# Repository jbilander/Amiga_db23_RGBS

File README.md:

# Amiga_DB23_RGBS
A small PCB with RGBS out from the Amiga d-sub db23 connector. Made with KiCad 5.1.2-1

### Updated v2 PCB

On request I made an updated PCB with the capacitor pads removed, 2 mm hole pitch giving two more GND holes. A little rerouting as well to provide for easier soldering when using cables with shielded wire pairs (signal + ground return). This PCB is not tested yet!

***

Update: On some cables I got a lot of noise/interference in the signal and needed to connect the shielding on the plugs on each end `d-sub metal shield <-> SCART metal shield` to get rid of it.

***

***

***

Let's solder this one. I used `220uF 16V size 1210` as coupling capacitors for the RGB pads. All resistors `size 1206`, I used the following values `R1: 330 Ohm, R2: 1K Ohm, R3: 75 Ohm`, following Stedy's guide here: The Ultimate SCART cable v1.1 http://www.ianstedman.co.uk/Amiga/amiga_hacks/Amiga_SCART/amiga_scart.html Not using pin 13 though as ground return but rather following this picture: https://ilesj.files.wordpress.com/2012/01/amiga_rgb-scart-diagram.png

***
I used an old DVI<->Vga cable that I butchered cutting off the plugs on both ends. I also found an old composite rca cable yellow-red-white laying around. I used the red-white part for the Audio. When making a cable with a SCART plug it makes sense to run the Left/Right audio wires inside the cable since the connector has both RGB video and stereo audio pins as standard. You can run the audio wires separately should you want to.

<br /><br />
I started with soldering the audio wires to the extension sides, holes with the "interconnected" symbol.
<br />

***

And then the rest, I used the three shielded wires for the RGB lines.

***

Moment of truth, hooking it up to the Amiga and yes it does work...I noticed I get more subtle vertical stripes with this cable then other Scart's I have tried, However I can still notice some "jailbars", check the last picture here from the game Another World. This is on my old Samsung LCD from 2005 that has seen better days. It is better on my plasma.

***

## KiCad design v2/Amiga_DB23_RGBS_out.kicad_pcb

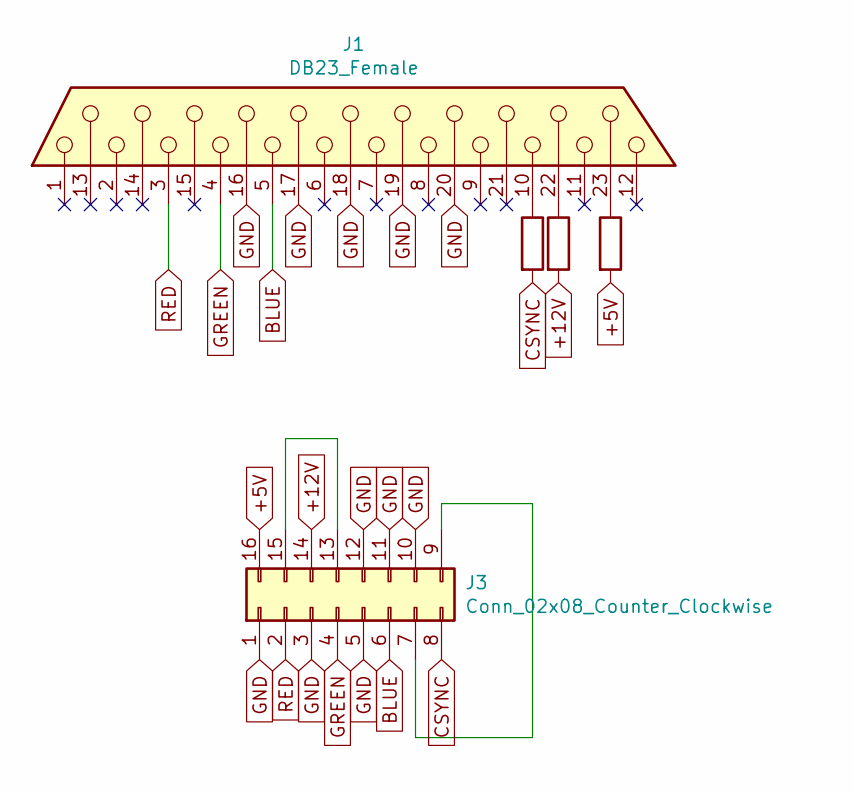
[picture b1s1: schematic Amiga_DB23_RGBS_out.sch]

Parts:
J1: DB23_Female; DSUB-23_Female_EdgeMount_P2.77mm
J3: Conn_02x08_Counter_Clockwise; PinHeader_2x08_P2.00mm_Vertical
R1: R330; R_1206_3216Metric_Pad1.42x1.75mm_HandSolder
R2: R; C_1206_3216Metric_Pad1.42x1.75mm_HandSolder
R3: R110; C_1206_3216Metric_Pad1.42x1.75mm_HandSolder

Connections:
+5V: J3.16, R3.2
+12V: J3.14, R2.2
BLUE: J1.5, J3.6
CSYNC: J3.8, R1.2
GND: J1.16, J1.17, J1.18, J1.19, J1.20, J3.1, J3.3, J3.5, J3.10, J3.11, J3.12
GREEN: J1.4, J3.4
unnamed: J1.10, R1.1
unnamed: J1.22, R2.1
unnamed: J1.23, R3.1
unnamed: J3.7, J3.9
unnamed: J3.13, J3.15
RED: J1.3, J3.2

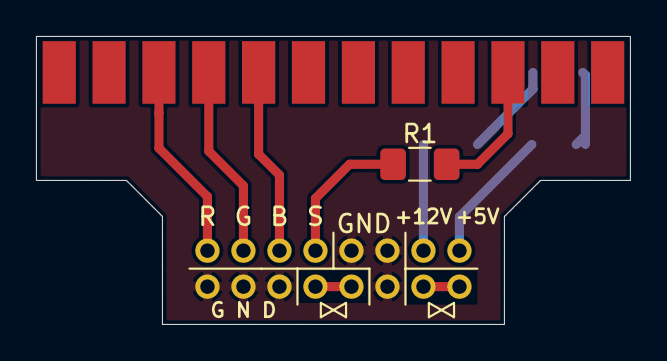
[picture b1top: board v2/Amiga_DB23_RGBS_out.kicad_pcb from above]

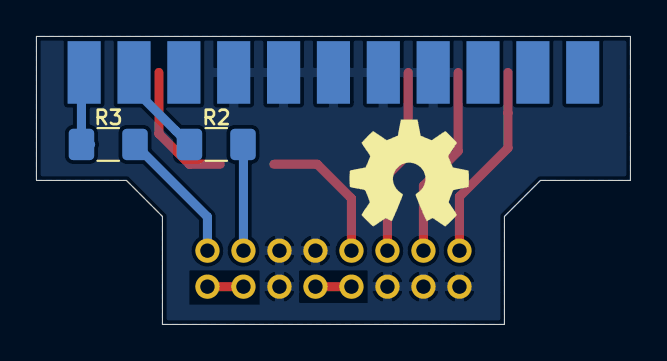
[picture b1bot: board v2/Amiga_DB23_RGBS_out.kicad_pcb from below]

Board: 2 copper layers, 33.0 x 16.0 mm, 5 parts (2 on the bottom side), 12 nets.

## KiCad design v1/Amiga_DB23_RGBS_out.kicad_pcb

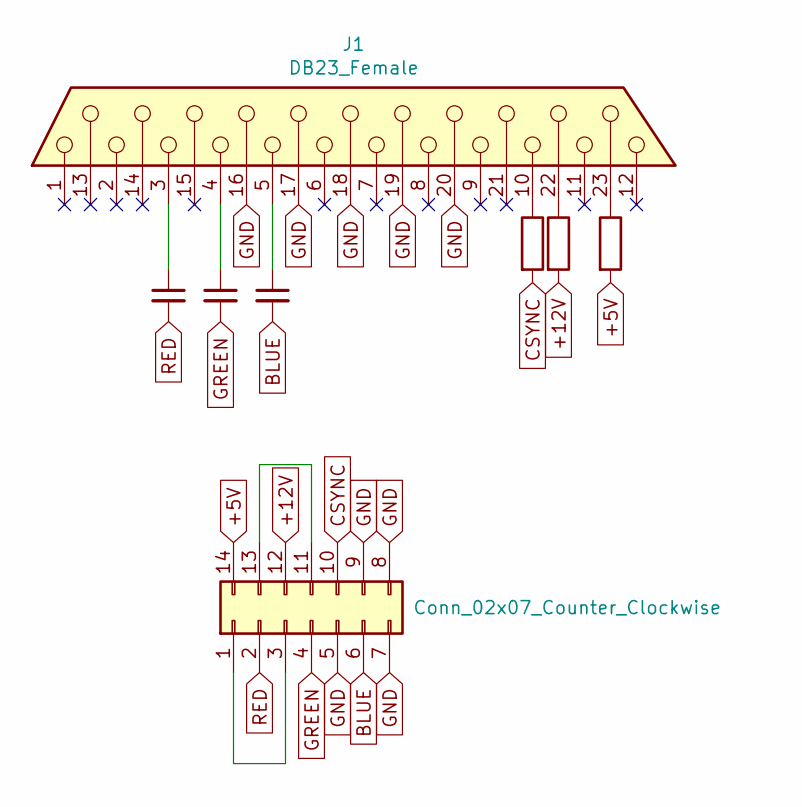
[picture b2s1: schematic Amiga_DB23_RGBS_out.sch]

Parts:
C1, C2, C3: C_Small; C_1210_3225Metric_Pad1.42x2.65mm_HandSolder
J1: DB23_Female; DSUB-23_Female_EdgeMount_P2.77mm
J2: Conn_02x07_Counter_Clockwise; PinHeader_2x07_P2.54mm_Vertical
R1: R330; R_1206_3216Metric_Pad1.42x1.75mm_HandSolder
R2: R; C_1206_3216Metric_Pad1.42x1.75mm_HandSolder
R3: R110; C_1206_3216Metric_Pad1.42x1.75mm_HandSolder

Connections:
+5V: J2.14, R3.2
+12V: J2.12, R2.2
BLUE: C3.2, J2.6
CSYNC: J2.10, R1.2
GND: J1.16, J1.17, J1.18, J1.19, J1.20, J2.5, J2.7, J2.8, J2.9
GREEN: C2.2, J2.4
unnamed: C1.1, J1.3
unnamed: C2.1, J1.4
unnamed: C3.1, J1.5
unnamed: J1.10, R1.1
unnamed: J1.22, R2.1
unnamed: J1.23, R3.1
unnamed: J2.1, J2.3
unnamed: J2.11, J2.13
RED: C1.2, J2.2

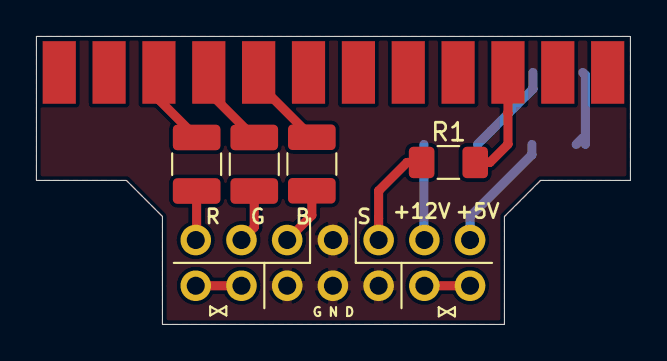
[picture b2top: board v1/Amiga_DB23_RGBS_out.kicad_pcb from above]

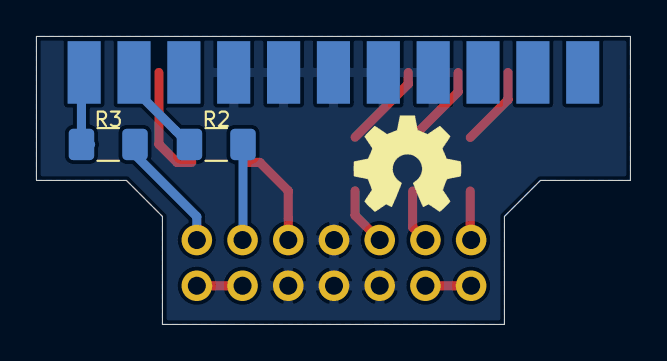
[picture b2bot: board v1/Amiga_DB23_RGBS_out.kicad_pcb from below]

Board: 2 copper layers, 33.0 x 16.0 mm, 8 parts (2 on the bottom side), 15 nets.

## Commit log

2020-02-26 added images
2020-02-26 Added source files
2020-02-27 added gitignore file
2020-07-03 added new version
